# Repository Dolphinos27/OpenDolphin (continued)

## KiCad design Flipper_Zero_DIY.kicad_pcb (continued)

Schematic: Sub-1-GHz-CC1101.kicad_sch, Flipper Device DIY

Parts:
C11, C25, C26, C27, C28, C32, C34, C35, C36, C39, C62, C89: 100nF; C_0603_1608Metric
C29, C30: 33pF; C_0603_1608Metric
C31, C33, C40, C84: 100pF; C_0603_1608Metric
C37, C38: 15 pF; C_0603_1608Metric
C42, C43: 1 µF; C_0603_1608Metric
C44, C45: 10pF; C_0603_1608Metric
C46: 1uF; C_0603_1608Metric
C47: 2.2uF; C_0603_1608Metric
D1: LED; LED_0603_1608Metric
L4: 22nH; L_0603_1608Metric
R10, R15, R32: R; R_0603_1608Metric
R11, R12, R13, R14: 22 Ohm; R_0603_1608Metric
U1: SKY13351-378LF; SOT-963
U2: ICE40UP5K-SG48ITR; QFN-48-1EP_7x7mm_P0.5mm_EP5.6x5.6mm
U3: W25Q16JVSSIQ; SOIC-8_3.9x4.9mm_P1.27mm
U4: AP2112K-1.2; SOT-23-5
U5: SX1276; QFN-28-1EP_6x6mm_P0.65mm_EP4.8x4.8mm
Y1: 32 MHz; Crystal_SMD_3225-4Pin_3.2x2.5mm

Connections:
/Sub-1-GHz-/(MISO): U2.45 (IOB_5b), U5.17 (MISO)
/Sub-1-GHz-/(MOSI): U2.44 (IOB_3b_G6), U5.18 (MOSI)
/Sub-1-GHz-/(NSS/CS): U2.47 (IOB_2a), U5.19 (NSS)
/Sub-1-GHz-/(SCK): U2.46 (IOB_0a), U5.16 (SCK)
/Sub-1-GHz-/DIO0SX1276: U2.2 (IOB_6a), U5.8 (DIO0)
/Sub-1-GHz-/DIO1SX1276: U2.3 (IOB_9b), U5.9 (DIO1)
/Sub-1-GHz-/DIO2SX1276: U2.48 (IOB_4a), U5.10 (DIO2)
/Sub-1-GHz-/NRESET4: R15.1, U2.4 (IOB_8a), U5.7 (~RESET)
GND: C11.1, C25.1, C26.1, C27.1, C28.1, C29.2, C30.2, C32.1, C34.1, C35.1, C36.1, C37.1, C38.1, C39.1, C42.1, C43.1, C44.2, C45.2, C46.1, C47.1, C62.1, C89.2, U1.2, U2.49 (GND), U3.4 (GND), U4.2 (GND), U5.15 (GND), U5.23 (GND), U5.26 (GND), U5.29 (GND); also elsewhere on the board
unnamed: C31.1, U1.3
unnamed: C31.2, C84.2
unnamed: C33.1, U1.1
unnamed: C33.2, C45.1, L4.2
unnamed: C40.2, C44.1, L4.1
unnamed: D1.1 (K), R32.2
unnamed: C30.1, U1.4, U2.6 (IOB_13b), U2.25 (IOT_36b), U5.20 (RXTX/RF_MOD)
unnamed: R12.2, U2.31 (IOT_42b)
unnamed: R13.2, U2.32 (IOT_43a)
unnamed: R11.2, U2.34 (IOT_44b)
unnamed: R14.2, U2.35 (IOT_46b_G0)
unnamed: U2.43 (IOT_49a), U5.11 (DIO3)
unnamed: U2.38 (IOT_50b), U5.13 (DIO5)
unnamed: U2.42 (IOT_51a), U5.12 (DIO4)
unnamed: R32.1, U2.7 (CDONE)
unnamed: C29.1, U1.6, U2.9 (IOB_16a)
unnamed: U2.14 (IOB_32a_SPI_SO), U3.5 (DI(IO0))
unnamed: U2.17 (IOB_33b_SPI_SI), U3.2 (DO(IO1))
unnamed: U2.15 (IOB_34a_SPI_SCK), U3.6 (CLK)
unnamed: U2.16 (IOB_35b_SPI_SS), U3.1 (~CS)
unnamed: C11.2, C25.2, C47.2, U2.5 (VCC), U2.29 (VCCPLL), U2.30 (VCC), U4.5 (VOUT)
unnamed: C40.1, U5.27 (PA_BOOST)
unnamed: C84.1, U5.21 (RFI_HF), U5.22 (RFO_HF)
unnamed: C42.2, U5.2 (VR_ANA)
unnamed: C43.2, U5.4 (VR_DIG)
unnamed: C32.2, C62.2, U5.25 (VR_PA)
unnamed: C38.2, U5.5 (XTA), Y1.2
unnamed: C37.2, U5.6 (XTB), Y1.1
PA4: R14.1; also elsewhere on the board
PA6: R10.2, U2.8 (~CRESET); also elsewhere on the board
SPI_R_MISO: R13.1; also elsewhere on the board
SPI_R_MOSI: R12.1; also elsewhere on the board
SPI_R_SCK: R11.1; also elsewhere on the board

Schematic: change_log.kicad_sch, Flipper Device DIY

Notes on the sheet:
- Changed "RS3221-3.3YF3" to "ADP151ACPZ-3.3-R7"
- Changed "BGS13S4N9E6327XTSA1" to "SKY13373-460LF"
LCD-Display
- Changed Buzzer BCE-MX8530A-03627 to AST0760MCTRQ
TODO:
Sub-1-GHz
- Changed the LCD-Display ERC12864FAMF03 to
POWER
iButton

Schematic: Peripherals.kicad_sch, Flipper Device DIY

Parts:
C59: 1uF; C_0402_1005Metric
C60, C61: 10uF; C_0603_1608Metric
DA4: LP5562TMX/NOPB; LP5562TMX-NOPB
R20, R25, R27, R30: 0; R_0402_1005Metric
R21, R22, R68: 47k; R_0402_1005Metric
R23, R31: 150; R_0402_1005Metric
R24, R26, R28, R29: 51; R_0402_1005Metric
R65, R66, R67: DNP; R_0402_1005Metric; not fitted
R69: 1k; R_0402_1005Metric
TP30: VIBRO; TestPoint_Pad_1.0x1.0mm
TP31: NFC_CS; TestPoint_Pad_1.0x1.0mm
TP32: RFID_CARRIER; TestPoint_Pad_1.0x1.0mm
TP33: IR_RX; TestPoint_Pad_1.0x1.0mm
TP34: IR_TX; TestPoint_Pad_1.0x1.0mm
TP35: SPEAKER; TestPoint_Pad_1.0x1.0mm
TP36: iBTN; TestPoint_Pad_1.0x1.0mm
TP37: RFID_IN; TestPoint_Pad_1.0x1.0mm
TP38: RFID_OUT; TestPoint_Pad_1.0x1.0mm
TP39: RFID_PULL; TestPoint_Pad_1.0x1.0mm
VD4: CLMUD-FKC-CHJNPM569ABB845343; SMD_RGB_LED_CLMUD-FKC-CHJNPM569ABB845343
VD5, VD6, VD7, VD8, VD9, VD10: ESD241B1W0201E6327XTSA1; D_0201_0603Metric
VD36: 1N4148X-TP; D_SOD-523
X6: FH34SRJ-18S-0.5SH(50); 18_pin_JST
X7: Micro_SD; microSD_HC_Hirose_DM3AT-SF-PEJM5

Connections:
GND: C59.2, C60.1, C61.1, DA4.A3 (CLK_32K), DA4.B1 (ADDR_SEL1), DA4.B2 (ADDR_SEL0), DA4.B3 (GND), VD5.1 (A1), VD6.1 (A1), VD7.1 (A1), VD8.1 (A1), VD9.1 (A1), VD10.1 (A1), X6.6, X6.8, X7.6 (VSS), X7.11 (SHIELD); also elsewhere on the board
I2C_SCL: DA4.C2 (SCL); also elsewhere on the board
I2C_SDA: DA4.C1 (SDA); also elsewhere on the board
IR_RX: TP33.1, X6.17; also elsewhere on the board
IR_TX: TP34.1, X6.16; also elsewhere on the board
LCD_LED: DA4.A1 (W); also elsewhere on the board
NFC_CS: TP31.1, X6.4; also elsewhere on the board
unnamed: DA4.A4 (B), R30.1
unnamed: DA4.B4 (G), R27.1
unnamed: DA4.C4 (R), R25.1
unnamed: R30.2, VD4.2 (BK)
unnamed: R27.2, VD4.3 (GK)
unnamed: R25.2, VD4.4 (RK)
unnamed: C60.2, C61.2, R20.1, R21.2, R22.2, R65.2, R66.2, R67.2, R68.2, VD6.2 (A2), X7.4 (VDD)
unnamed: R69.1, VD36.1 (K)
unnamed: R29.2, X6.9
unnamed: R26.2, X7.5 (CLK)
unnamed: R24.2, X7.3 (CMD)
unnamed: R28.2, X7.7 (DAT0)
unnamed: R21.1, X7.8 (DAT1)
unnamed: R22.1, X7.1 (DAT2)
unnamed: R23.1, X7.2 (DAT3/CD)
unnamed: R31.2, X7.10 (SW_DTCT)
RESET: DA4.C3 (EN_VCC); also elsewhere on the board
RFID_CARRIER: TP32.1, X6.18; also elsewhere on the board
RFID_OUT: TP38.1, X6.12; also elsewhere on the board
RFID_PULL: TP39.1, X6.11; also elsewhere on the board
RFID_RF_IN: TP37.1, X6.5; also elsewhere on the board
SD_CD: R31.1, R68.1, VD5.2 (A2); also elsewhere on the board
SD_CS: R23.2, VD10.2 (A2); also elsewhere on the board
SPEAKER: TP35.1, X6.15; also elsewhere on the board
SPI_D_MISO: R28.1, R65.1, VD7.2 (A2); also elsewhere on the board
SPI_D_MOSI: R24.1, R26.1, R66.1, R67.1, VD8.2 (A2), VD9.2 (A2); also elsewhere on the board
SPI_R_MISO: R29.1; also elsewhere on the board
SPI_R_MOSI: X6.13; also elsewhere on the board
SPI_R_SCK: X6.7; also elsewhere on the board
SYS: C59.1, DA4.A2 (VDD), VD4.1 (A), X6.1, X6.2; also elsewhere on the board
USB 5V: VD36.2 (A); also elsewhere on the board
VIBRO: TP30.1, X6.10; also elsewhere on the board
ext3.3V: R20.2; also elsewhere on the board
iBTN: R69.2, TP36.1, X6.14; also elsewhere on the board

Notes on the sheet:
SD-Card
GND
SYS
iBTN
ST25_MOSI
RFID_CARRIER
ST25_MISO
LED Driver
PCB-PCB Connector
RFID_PULL
RFID_IN
+3.3V
ST25_SCLK
VIBRO
IR_TX
ST25_BSS
LED-Driver
SPEAKER
IR_RX
RFID_OUT

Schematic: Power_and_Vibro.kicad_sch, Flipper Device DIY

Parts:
Q1: NMOS; SOT-23
RC35: 10uF; C_0603_1608Metric
RC36: 22uF; C_0603_1608Metric
RDA1: FAN48610BUC50X; WLCSP9_1P2X1P2_ONS
RL3: 470nH; L_0603_1608Metric
RR3: 22; R_0603_1608Metric
RR4: 150; R_0603_1608Metric
RR5: 10k; R_0603_1608Metric
RVD2: 1N4148X-TP; D_0603_1608Metric
RX3: FH34SRJ-18S-0.5SH(50); SOIC-18W_7.5x11.6mm_P1.27mm
RX10: PCB_PAD; R_0603_1608Metric
TP69: IR_RX; TestPoint_Pad_D1.0mm
TP70: IR_TX; TestPoint_Pad_D1.0mm
TP71: SPEAKER; TestPoint_Pad_D1.0mm
TP72: iBTN; TestPoint_Pad_D1.0mm
TP73: SPI_R_MOSI; TestPoint_Pad_D1.0mm
TP74: NFC_CS; TestPoint_Pad_D1.0mm
TP75: VIBRO1; TestPoint_Pad_D1.0mm
TP76: RFID_OUT; TestPoint_Pad_D1.0mm
TP77: RFID_PULL; TestPoint_Pad_D1.0mm
TP78: SPI_R_MISO; TestPoint_Pad_D1.0mm
TP79: SPI_R_SCK; TestPoint_Pad_D1.0mm
TP80: RFID_RF_IN; TestPoint_Pad_D1.0mm
TP81: GND2
TP82: GND3
TP83: RFID_CARRIER; TestPoint_Pad_D1.0mm
TP84: VIBRO2; TestPoint_Pad_D1.0mm
TP85: VIBRO3; TestPoint_Pad_D1.0mm
TP86: SYS1
TP87: SYS2
TP88: 5V_1
TP89: 5V_2
TP90: 3V_1
TP91: 3V_2
TP92: GND_1
TP93: GND_2

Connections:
+5V: RC36.1, RDA1.A1 (VOUT), RDA1.A2 (VOUT), TP88.1, TP89.1; also elsewhere on the board
GND: Q1.3 (S), RC35.2, RC36.2, RDA1.C1 (PGND), RDA1.C2 (PGND), RDA1.C3 (AGND), RR5.2, RX3.6, RX3.8, TP81.1, TP82.1, TP92.1, TP93.1; also elsewhere on the board
IR_RX: RX3.17, TP69.1; also elsewhere on the board
IR_TX: RX3.16, TP70.1; also elsewhere on the board
NFC_CS: RX3.4, TP74.1; also elsewhere on the board
unnamed: Q1.1 (D), RVD2.2 (A), RX10.2, TP84.1
unnamed: Q1.2 (G), RR4.1, RR5.1
unnamed: RDA1.B1 (SW), RDA1.B2 (SW), RL3.2
unnamed: RR3.2, RVD2.1 (K), RX10.1, TP85.1
unnamed: RR4.2, RX3.10, TP75.1
RFID_CARRIER: RX3.18, TP83.1; also elsewhere on the board
RFID_OUT: RX3.12, TP76.1; also elsewhere on the board
RFID_PULL: RX3.11, TP77.1; also elsewhere on the board
RFID_RF_IN: RX3.5, TP80.1; also elsewhere on the board
SPEAKER: RX3.15, TP71.1; also elsewhere on the board
SPI_R_MISO: RX3.9, TP78.1; also elsewhere on the board
SPI_R_MOSI: RX3.13, TP73.1; also elsewhere on the board
SPI_R_SCK: RX3.7, TP79.1; also elsewhere on the board
SYS: RC35.1, RDA1.A3 (VIN), RDA1.B3 (EN), RL3.1, RR3.1, RX3.1, RX3.2, TP86.1, TP87.1; also elsewhere on the board
iBTN: RX3.14, TP72.1; also elsewhere on the board

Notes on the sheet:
RFID_PULL
VIBRO
Vibro+
RFID_CARROER
SYS
ST25_MOSI
ST25 SCLK
RFID_IN
GND
ST25 BSS
IR_TX
SPEAKER
Vibro-
IR_RX
RFID_OUT
+3.3V
iBTN
ST25_MISO

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
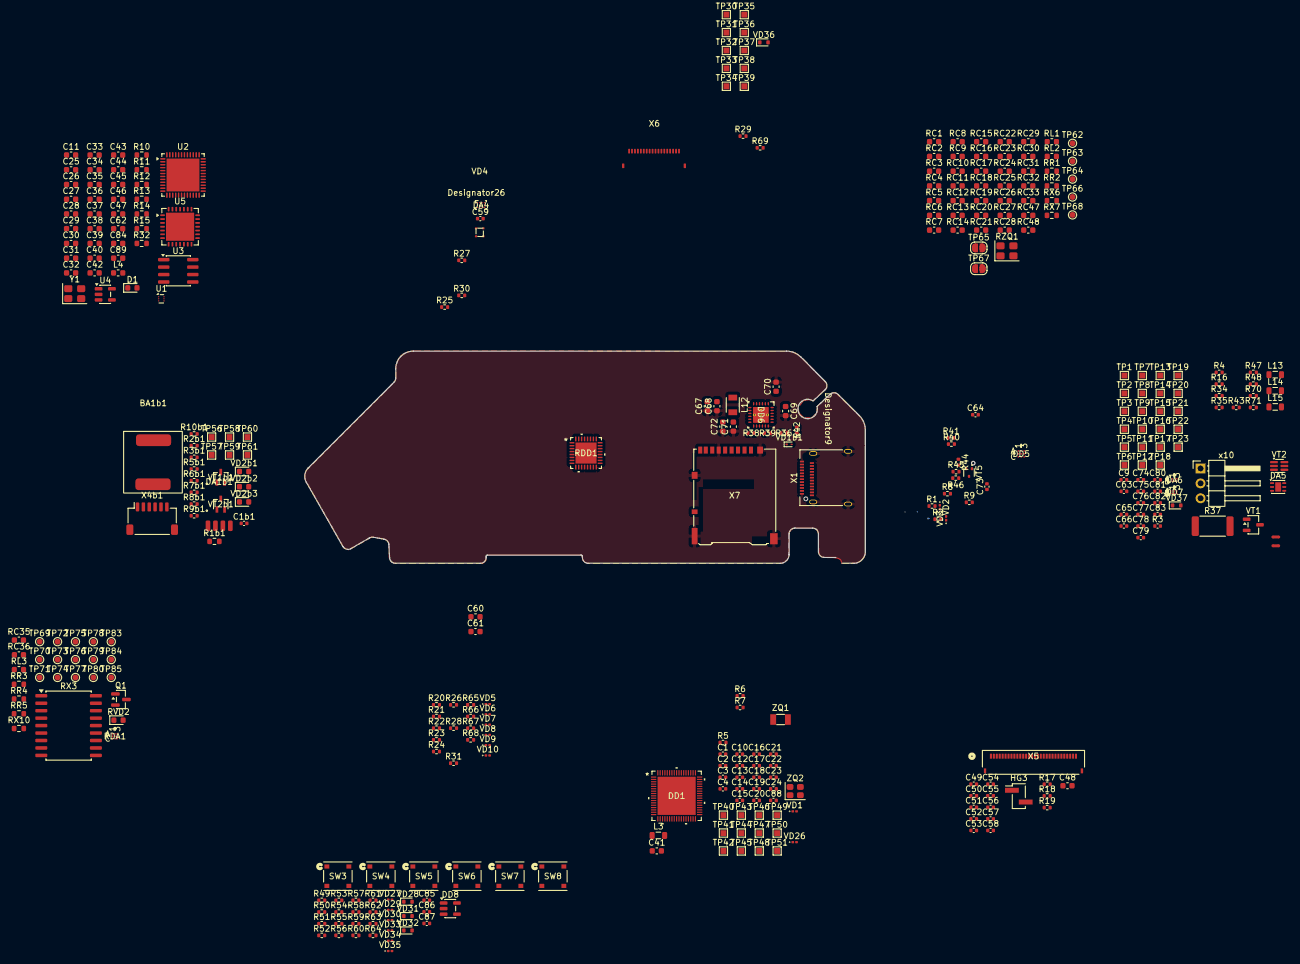
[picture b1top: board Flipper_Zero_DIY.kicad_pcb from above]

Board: 4 copper layers, 363 parts (0 on the bottom side), 192 nets.

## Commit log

2026-02-06 Add files via upload
    old pictures
